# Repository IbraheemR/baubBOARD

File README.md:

# baubBOARD - a minimalist IO board for the RPi CM4

Contains only 5v input and ethernet port

Will eventually stack to enable super DENSE compute clusters

Will probably need some beefy cooling.

Ultimate COMPUTE

TODO:

- Should probably add reverse voltage/polyfuse protection
- Make >smaller<
- How to reduce stack height? Or are we limited by the thickness of ethernet port
  - Could Make 2 offset PCBs to stagger ethernet ports
  - Use custom port?

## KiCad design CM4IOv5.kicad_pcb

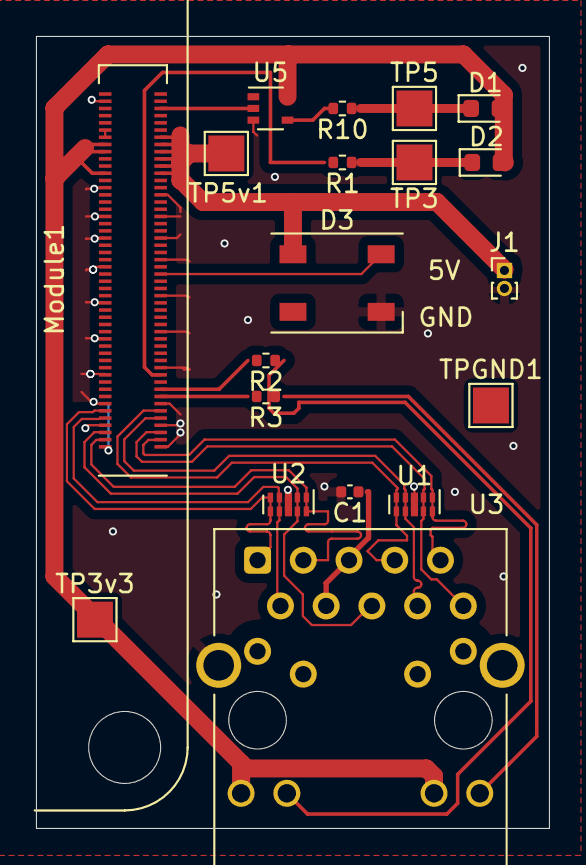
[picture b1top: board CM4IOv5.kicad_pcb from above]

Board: 2 copper layers, 28.5 x 44.0 mm, 19 parts (0 on the bottom side), 23 nets.

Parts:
C1: 100n; C_0402_1005Metric
D1: LED Red; LED_0603_1608Metric
D2: LED Green; LED_0603_1608Metric
D3: SK6812; LED_SK6812_PLCC4_5.0x5.0mm_P3.2mm
J1: Conn_01x02_Male; PinHeader_1x02_P1.00mm_Vertical
Module1: ComputeModule4; Raspberry-Pi-4-Compute-Module
R1, R10: 1k; R_0402_1005Metric
R2, R3: 470R; R_0402_1005Metric
TP3, TP3v3, TP5, TP5v1: TestPoint; TestPoint_Pad_2.0x2.0mm
TPGND1: TestPoint; TestPoint_Pad_2.0x2.0mm
U1, U2: TPD4EUSB30; USON-10_2.5x1.0mm_P0.5mm
U3: MagJack-A70-112-331N126; TRJG0926HENL
U5: 74LVC1G07SE-7; SOT-353_SC-70-5

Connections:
/CM4_GPIO ( Ethernet, GPIO, SDCARD)/+1.8v: Module1.88 (+1.8v_(Output)), Module1.90 (+1.8v_(Output))
/CM4_GPIO ( Ethernet, GPIO, SDCARD)/+3.3v: D1.2 (A), D2.2 (A), Module1.78 (GPIO_VREF(1.8v/3.3v_Input)), Module1.84 (+3.3v_(Output)), Module1.86 (+3.3v_(Output)), TP3v3.1, U3.15 (LEDG_A), U3.17 (LEDY_A), U5.5 (VCC)
/CM4_GPIO ( Ethernet, GPIO, SDCARD)/+5v: D3.3 (VDD), J1.1, Module1.77 (+5v_(Input)), Module1.79 (+5v_(Input)), Module1.81 (+5v_(Input)), Module1.83 (+5v_(Input)), Module1.85 (+5v_(Input)), Module1.87 (+5v_(Input)), TP5v1.1
/CM4_GPIO ( Ethernet, GPIO, SDCARD)/ETH_LEDG: Module1.17 (Ethernet_nLED2(3.3v)), R2.2
/CM4_GPIO ( Ethernet, GPIO, SDCARD)/ETH_LEDY: Module1.15 (Ethernet_nLED3(3.3v)), R3.2
/CM4_GPIO ( Ethernet, GPIO, SDCARD)/GPIO18: D3.2 (DIN), Module1.49 (GPIO18)
/CM4_GPIO ( Ethernet, GPIO, SDCARD)/TRD0_N: Module1.10 (Ethernet_Pair0_N), U2.4 (D2+), U2.7, U3.2 (TRD0-)
/CM4_GPIO ( Ethernet, GPIO, SDCARD)/TRD0_P: Module1.12 (Ethernet_Pair0_P), U2.5 (D2-), U2.6, U3.1 (TRD0+)
/CM4_GPIO ( Ethernet, GPIO, SDCARD)/TRD1_N: Module1.6 (Ethernet_Pair1_N), U2.2 (D1-), U2.9, U3.6 (TRD1-)
/CM4_GPIO ( Ethernet, GPIO, SDCARD)/TRD1_P: Module1.4 (Ethernet_Pair1_P), U2.1 (D1+), U2.10, U3.3 (TRD1+)
/CM4_GPIO ( Ethernet, GPIO, SDCARD)/TRD2_N: Module1.9 (Ethernet_Pair2_N), U1.4 (D2+), U1.7, U3.8 (TRD2-)
/CM4_GPIO ( Ethernet, GPIO, SDCARD)/TRD2_P: Module1.11 (Ethernet_Pair2_P), U1.5 (D2-), U1.6, U3.7 (TRD2+)
/CM4_GPIO ( Ethernet, GPIO, SDCARD)/TRD3_N: Module1.5 (Ethernet_Pair3_N), U1.2 (D1-), U1.9, U3.10 (TRD3-)
/CM4_GPIO ( Ethernet, GPIO, SDCARD)/TRD3_P: Module1.3 (Ethernet_Pair3_P), U1.1 (D1+), U1.10, U3.9 (TRD3+)
/CM4_GPIO ( Ethernet, GPIO, SDCARD)/nLED_Activity: Module1.21 (PI_nLED_Activity), R1.2
/CM4_GPIO ( Ethernet, GPIO, SDCARD)/nPWR_LED: Module1.95 (nPI_LED_PWR), U5.2
GND: C1.2, D3.1 (VSS), J1.2, Module1.1 (GND), Module1.2 (GND), Module1.7 (GND), Module1.8 (GND), Module1.13 (GND), Module1.14 (GND), Module1.22 (GND), Module1.23 (GND), Module1.32 (GND), Module1.33 (GND), Module1.42 (GND), Module1.43 (GND), Module1.52 (GND), Module1.53 (GND), Module1.59 (GND), Module1.60 (GND), Module1.65 (GND), Module1.66 (GND), Module1.71 (GND), Module1.74 (GND), Module1.98 (GND), U1.3 (GND), U1.8 (GND), U2.3 (GND), U2.8 (GND), U3.19 (SHIELD), U3.20 (SHIELD), U5.3 (GND)
unnamed: C1.1, U3.4 (CT), U3.5 (CT)
unnamed: D1.1 (K), R10.1, TP5.1
unnamed: D2.1 (K), R1.1, TP3.1
unnamed: R2.1, U3.16 (LEDG_K)
unnamed: R3.1, U3.18 (LEDY_K)
unnamed: R10.2, U5.4

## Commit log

2021-06-17 Add files (currently working on v0.2)
2021-06-17 Add gitignore and remove junk files
2021-06-20 Add TODO & SK6812 LED
